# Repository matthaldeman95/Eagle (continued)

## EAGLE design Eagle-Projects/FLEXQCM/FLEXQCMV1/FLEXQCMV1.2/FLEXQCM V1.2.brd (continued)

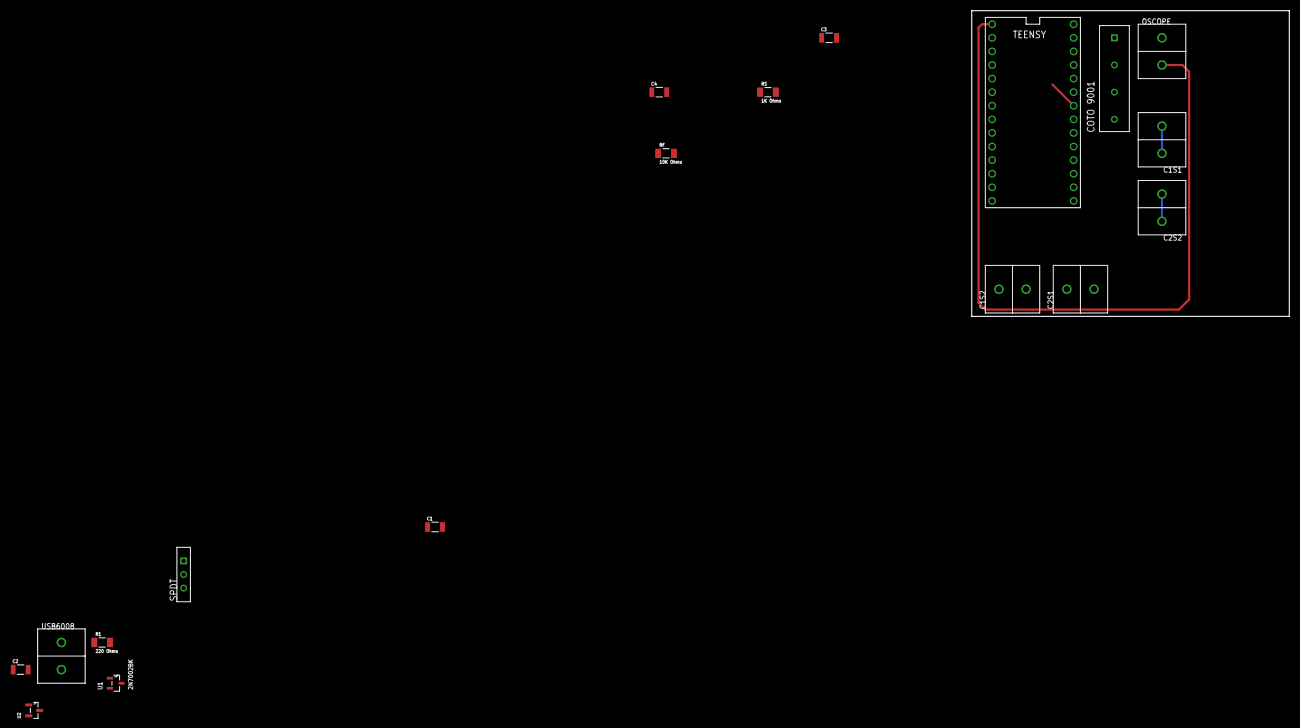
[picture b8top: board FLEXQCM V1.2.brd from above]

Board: 2 copper layers, 59.4 x 57.1 mm, 18 parts (0 on the bottom side), 12 nets.

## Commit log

2016-04-16 fixed file name for windows compatibility
2016-04-16 New solar panel board, revision 3, t-shape
2016-05-19 Commit of all RockSat-C 2016 payload designs.
